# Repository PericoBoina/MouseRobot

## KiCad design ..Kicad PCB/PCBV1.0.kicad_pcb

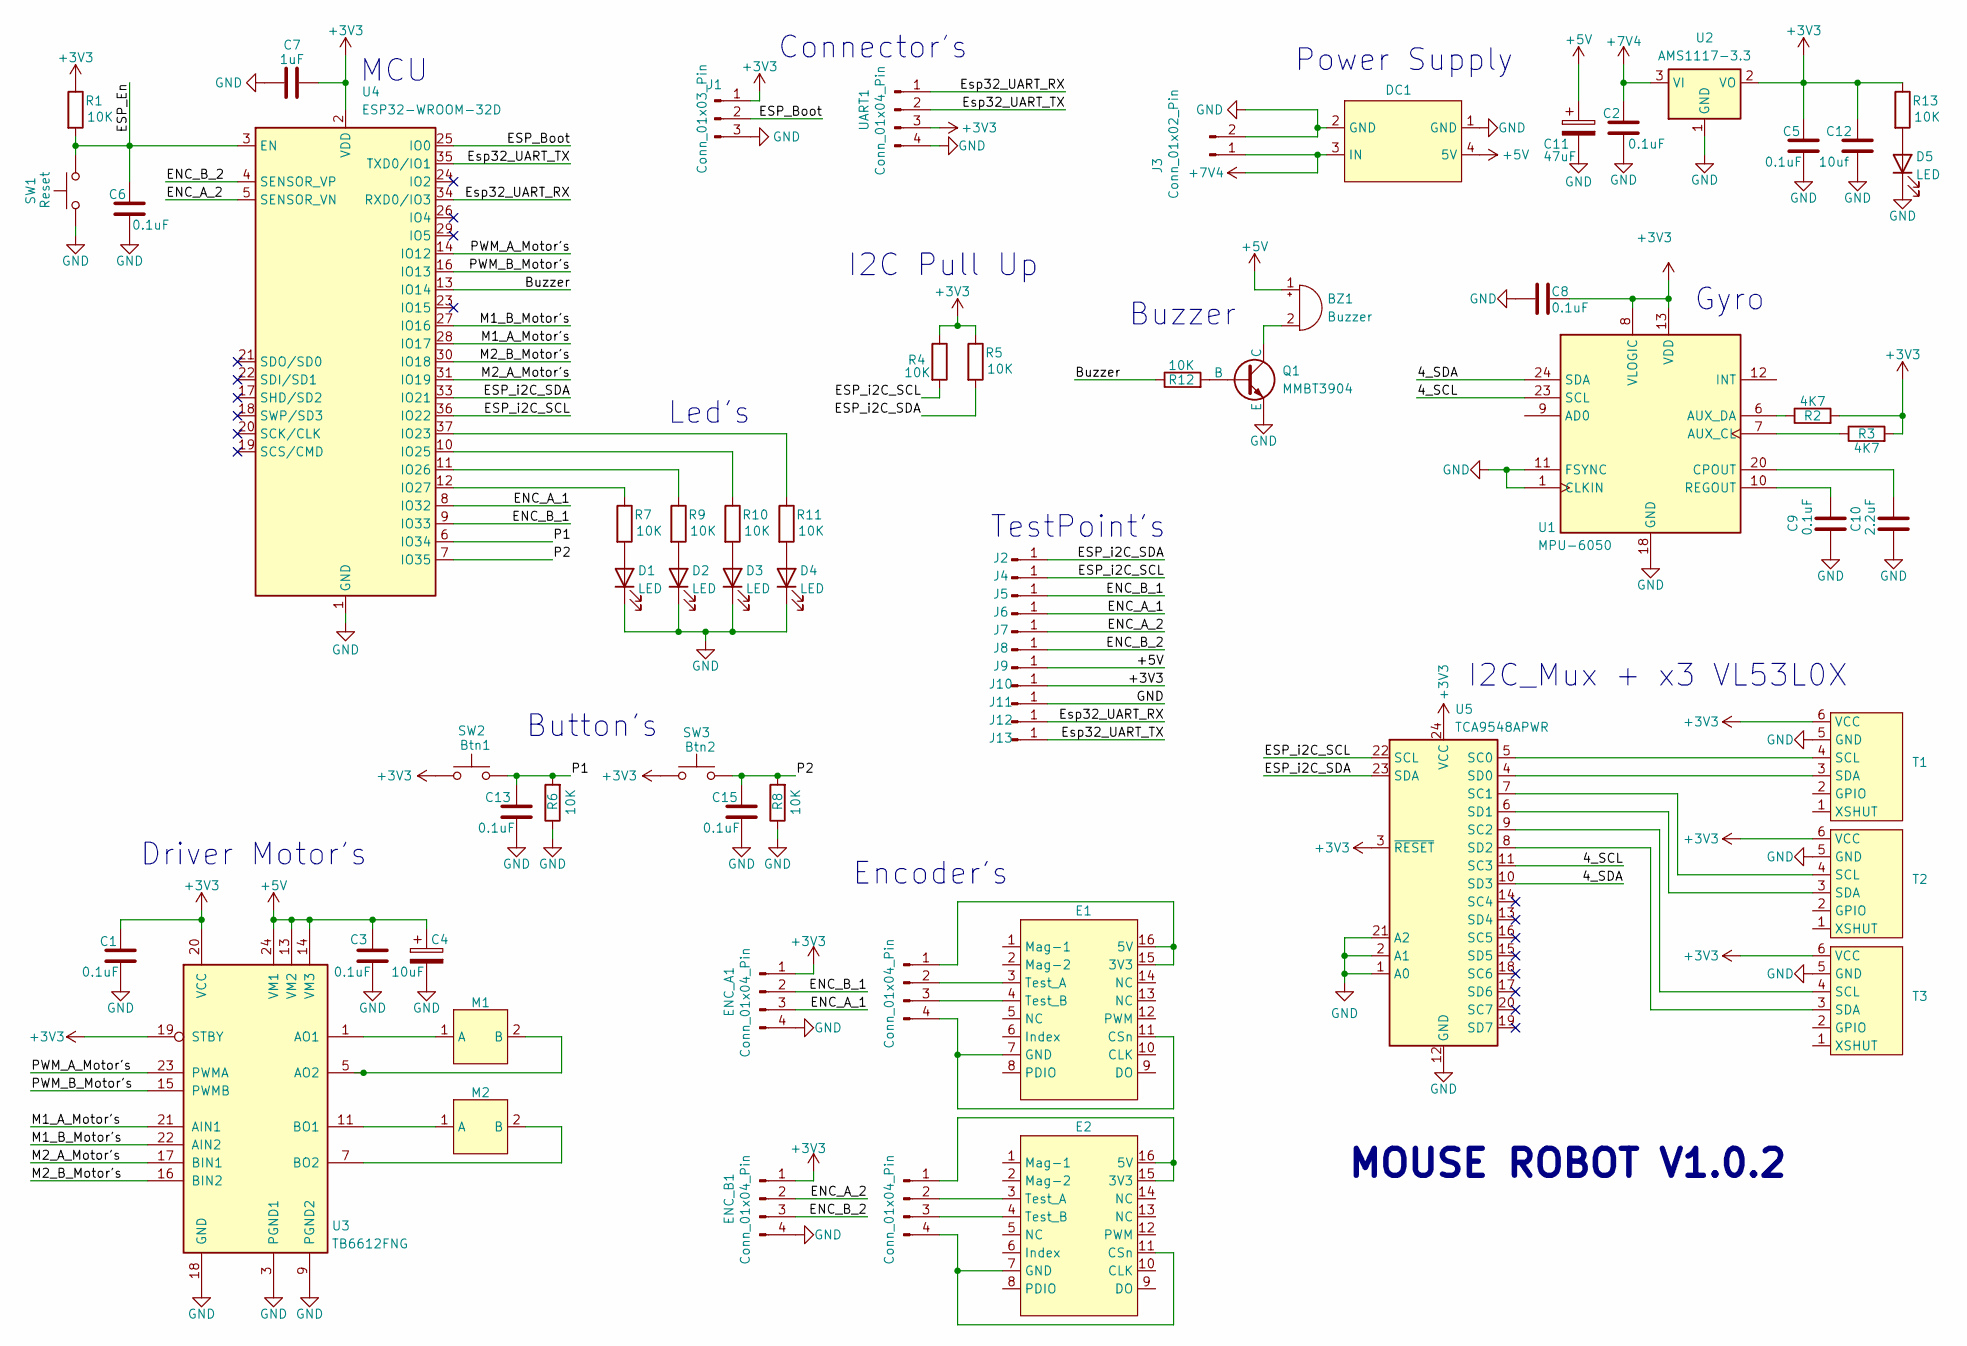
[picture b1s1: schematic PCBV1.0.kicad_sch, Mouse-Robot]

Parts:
BZ1: Buzzer; MLT2575
C1, C2, C3, C5, C6, C8, C9, C13, C15: 0.1uF; C_0805_2012Metric
C4: 10uF; CP_EIA-3216-18_Kemet-A
C7: 1uF; C_0805_2012Metric
C10: 2.2uF; C_0805_2012Metric
C11: 47uF; CP_Elec_6.3x5.4
C12: 10uf; C_0805_2012Metric
D1, D2, D3, D4, D5: LED; LED_0805_2012Metric
DC1: 5v MODULE
E1, E2: SSOP-16_5.3x6.2mm_P0.65mm
ENC_A1: Conn_01x04_Pin; PinHeader_1x04_P2.54mm_Vertical
ENC_B1, ENC_B2, ENC_B3: Conn_01x04_Pin; PinHeader_1x04_P2.54mm_Vertical
J1: Conn_01x03_Pin; PinHeader_1x03_P2.54mm_Vertical
J2, J4, J5, J6, J7, J8, J9, J10, J11, J12, J13: Conn_01x01_Pin; TestPoint_Pad_D1.0mm
J3: Conn_01x02_Pin; JST_XH_B2B-XH-AM_1x02_P2.50mm_Vertical
M1, M2: M
Q1: MMBT3904; SOT-23
R1, R4, R5, R6, R7, R8, R9, R10, R11, R12, R13: 10K; R_0805_2012Metric
R2, R3: 4K7; R_0805_2012Metric
SW1: Reset; SW_SPST_SKQG_WithStem
SW2: Btn1; SW_SPST_SKQG_WithStem
SW3: Btn2; SW_SPST_SKQG_WithStem
T1, T2, T3: PinHeader_1x06_P2.54mm_Vertical
U1: MPU-6050; InvenSense_QFN-24_4x4mm_P0.5mm
U2: AMS1117-3.3; SOT-223-3_TabPin2
U3: TB6612FNG; SSOP-24_5.3x8.2mm_P0.65mm
U4: ESP32-WROOM-32D
U5: TCA9548APWR; TSSOP-24_4.4x7.8mm_P0.65mm
UART1: Conn_01x04_Pin; PinHeader_1x04_P2.54mm_Vertical

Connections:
+3V3: C1.1, C5.1, C7.1, C8.2, C12.1, ENC_A1.1, ENC_B1.1, J1.1, J10.1, R1.1, R2.2, R3.2, R4.1, R5.1, R13.1, SW2.1, SW3.1, T1.6 (VCC), T2.6 (VCC), T3.6 (VCC), U1.8 (VLOGIC), U1.13 (VDD), U2.2 (VO), U3.19 (STBY), U3.20 (VCC), U4.2 (VDD), U5.3 (~RESET), U5.24 (VCC), UART1.3
+5V: BZ1.1 (+), C3.1, C4.1, C11.1, DC1.4 (5V), J9.1, U3.13 (VM2), U3.14 (VM3), U3.24 (VM1)
+7V4: C2.1, DC1.3 (IN), J3.1, U2.3 (VI)
/4_SCL: U1.23 (SCL), U5.11 (SC3)
/4_SDA: U1.24 (SDA), U5.10 (SD3)
/Buzzer: R12.1, U4.13 (IO14)
/ENC_A_1: ENC_A1.3, J6.1, U4.8 (IO32)
/ENC_A_2: ENC_B1.2, J7.1, U4.5 (SENSOR_VN)
/ENC_B_1: ENC_A1.2, J5.1, U4.9 (IO33)
/ENC_B_2: ENC_B1.3, J8.1, U4.4 (SENSOR_VP)
/ESP_Boot: J1.2, U4.25 (IO0)
/ESP_En: C6.1, R1.2, SW1.2, U4.3 (EN)
/ESP_i2C_SCL: J4.1, R4.2, U4.36 (IO22), U5.22 (SCL)
/ESP_i2C_SDA: J2.1, R5.2, U4.33 (IO21), U5.23 (SDA)
/Esp32_UART_RX: J12.1, U4.34 (RXD0/IO3), UART1.1
/Esp32_UART_TX: J13.1, U4.35 (TXD0/IO1), UART1.2
/M1_A_Motor's: U3.21 (AIN1), U4.28 (IO17)
/M1_B_Motor's: U3.22 (AIN2), U4.27 (IO16)
/M2_A_Motor's: U3.17 (BIN1), U4.31 (IO19)
/M2_B_Motor's: U3.16 (BIN2), U4.30 (IO18)
/P1: C13.1, R6.2, SW2.2, U4.6 (IO34)
/P2: C15.1, R8.2, SW3.2, U4.7 (IO35)
/PWM_A_Motor's: U3.23 (PWMA), U4.14 (IO12)
/PWM_B_Motor's: U3.15 (PWMB), U4.16 (IO13)
GND: C1.2, C2.2, C3.2, C4.2, C5.2, C6.2, C7.2, C8.1, C9.2, C10.2, C11.2, C12.2, C13.2, C15.2, D1.1 (K), D2.1 (K), D3.1 (K), D4.1 (K), D5.1 (K), DC1.1 (GND), DC1.2 (GND), ENC_A1.4, ENC_B1.4, J1.3, J3.2, J11.1, Q1.3 (E), R6.1, R8.1, SW1.1, T1.5 (GND), T2.5 (GND), T3.5 (GND), U1.1 (CLKIN), U1.11 (FSYNC), U1.18 (GND), U2.1 (GND), U3.3 (PGND1), U3.4 (PGND1), U3.9 (PGND2), U3.10 (PGND2), U3.18 (GND), U4.1 (GND), U4.15 (GND), U4.38 (GND), U4.39 (GND), U5.1 (A0), U5.2 (A1), U5.12 (GND), U5.21 (A2), UART1.4
unnamed: BZ1.2 (-), Q1.1 (C)
unnamed: D1.2 (A), R7.2
unnamed: D2.2 (A), R9.2
unnamed: D3.2 (A), R10.2
unnamed: D4.2 (A), R11.2
unnamed: D5.2 (A), R13.2
unnamed: E1.15 (3V3), E1.16 (5V), ENC_B2.1
unnamed: E1.7 (GND), E1.11 (CSn), ENC_B2.4
unnamed: E1.3 (Test_A), ENC_B2.2
unnamed: E1.4 (Test_B), ENC_B2.3
unnamed: E2.15 (3V3), E2.16 (5V), ENC_B3.1
unnamed: E2.7 (GND), E2.11 (CSn), ENC_B3.4
unnamed: E2.3 (Test_A), ENC_B3.2
unnamed: E2.4 (Test_B), ENC_B3.3
unnamed: M1.1 (A), U3.1 (AO1), U3.2 (AO1)
unnamed: M1.2 (B), U3.5 (AO2), U3.6 (AO2)
unnamed: M2.1 (A), U3.11 (BO1), U3.12 (BO1)
unnamed: M2.2 (B), U3.7 (BO2), U3.8 (BO2)
unnamed: Q1.2 (B), R12.2
unnamed: T1.4 (SCL), U5.5 (SC0)
unnamed: T1.3 (SDA), U5.4 (SD0)
unnamed: T2.4 (SCL), U5.7 (SC1)
unnamed: T2.3 (SDA), U5.6 (SD1)
unnamed: T3.4 (SCL), U5.9 (SC2)
unnamed: T3.3 (SDA), U5.8 (SD2)
unnamed: R3.1, U1.7 (AUX_CL)
unnamed: R2.1, U1.6 (AUX_DA)
unnamed: C10.1, U1.20 (CPOUT)
unnamed: C9.1, U1.10 (REGOUT)
unnamed: R11.1, U4.37 (IO23)
unnamed: R10.1, U4.10 (IO25)
unnamed: R9.1, U4.11 (IO26)
unnamed: R7.1, U4.12 (IO27)

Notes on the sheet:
Power Supply
TestPoint's
MCU
Encoder's
Buzzer
Driver Motor's
Button's
Led's
Connector's
Gyro
I2C_Mux + x3 VL53L0X
MOUSE ROBOT V1.0.2
I2C Pull Up

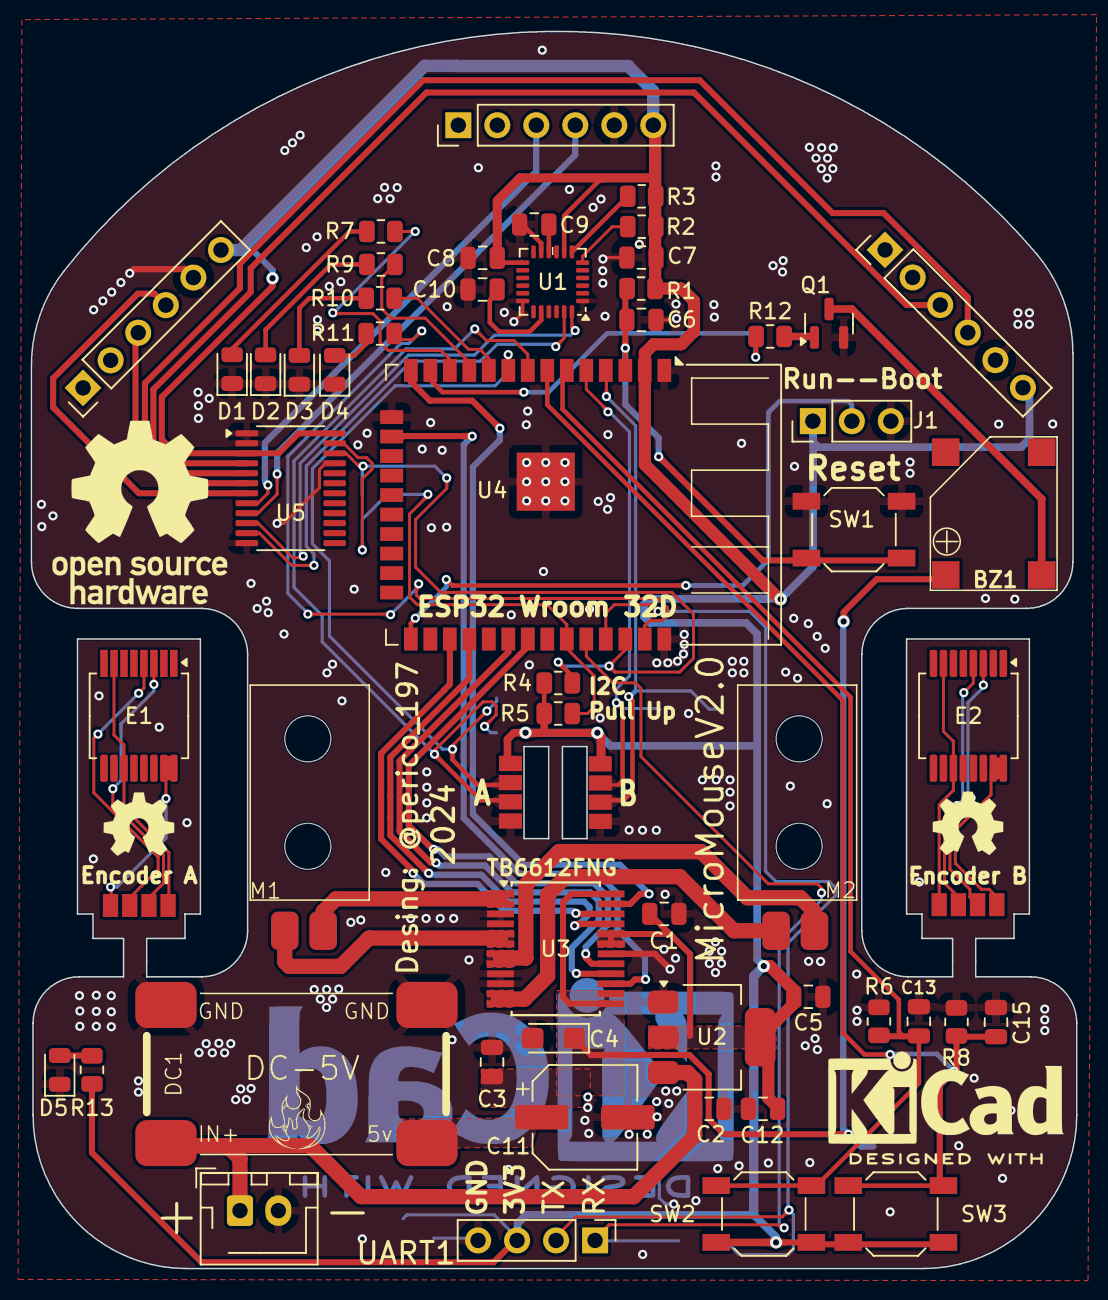
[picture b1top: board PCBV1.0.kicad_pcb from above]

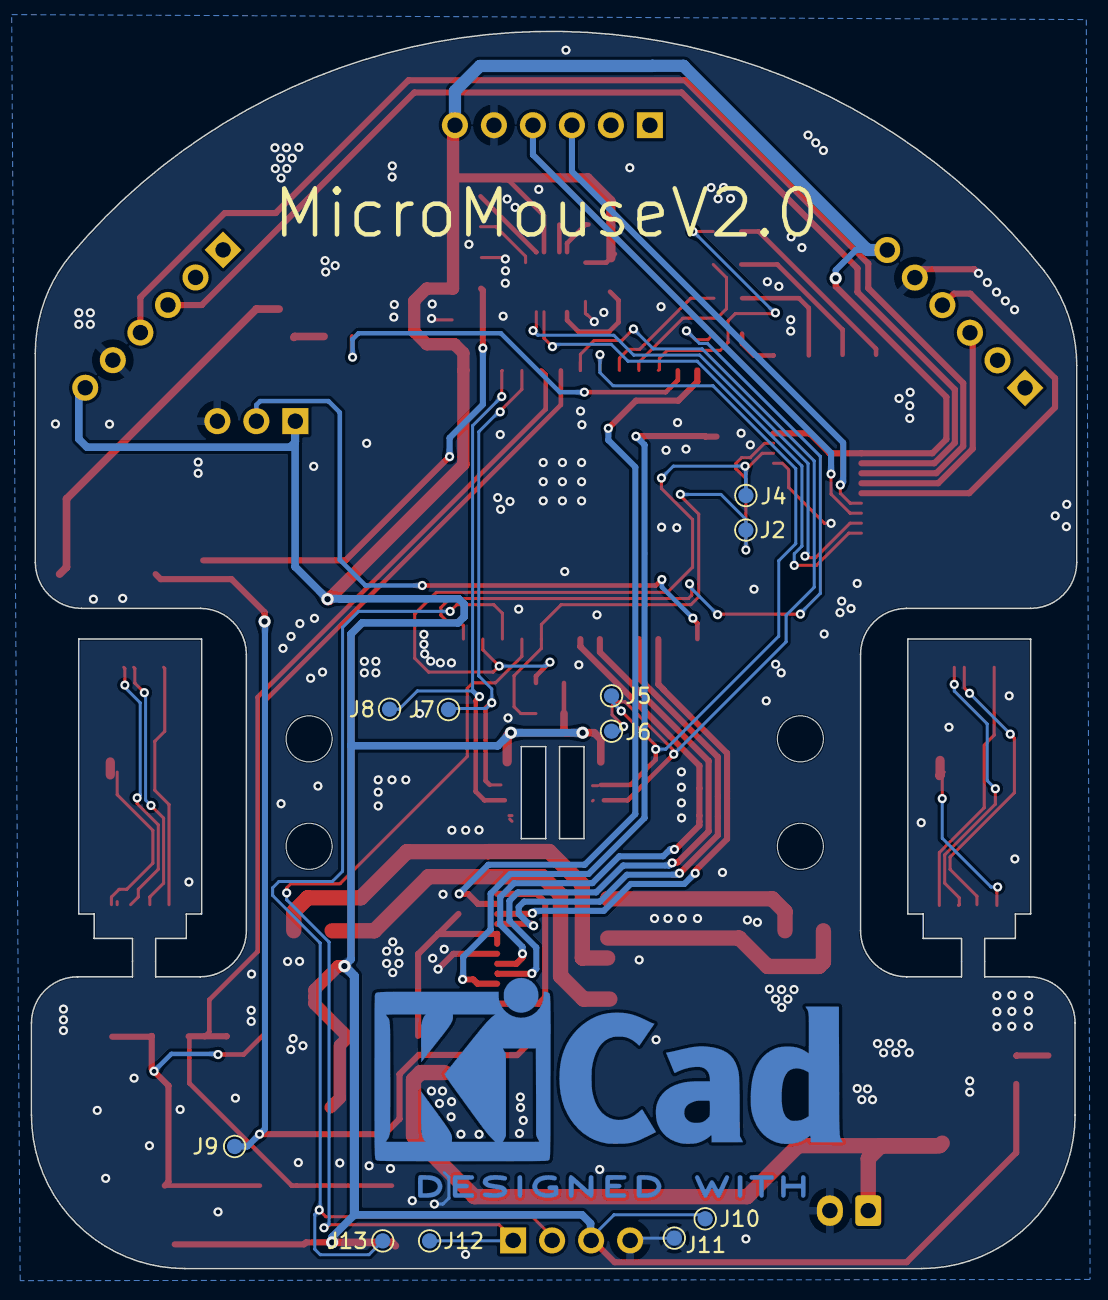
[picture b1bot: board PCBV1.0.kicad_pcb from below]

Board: 2 copper layers, 68.1 x 80.6 mm, 68 parts (11 on the bottom side), 58 nets.
